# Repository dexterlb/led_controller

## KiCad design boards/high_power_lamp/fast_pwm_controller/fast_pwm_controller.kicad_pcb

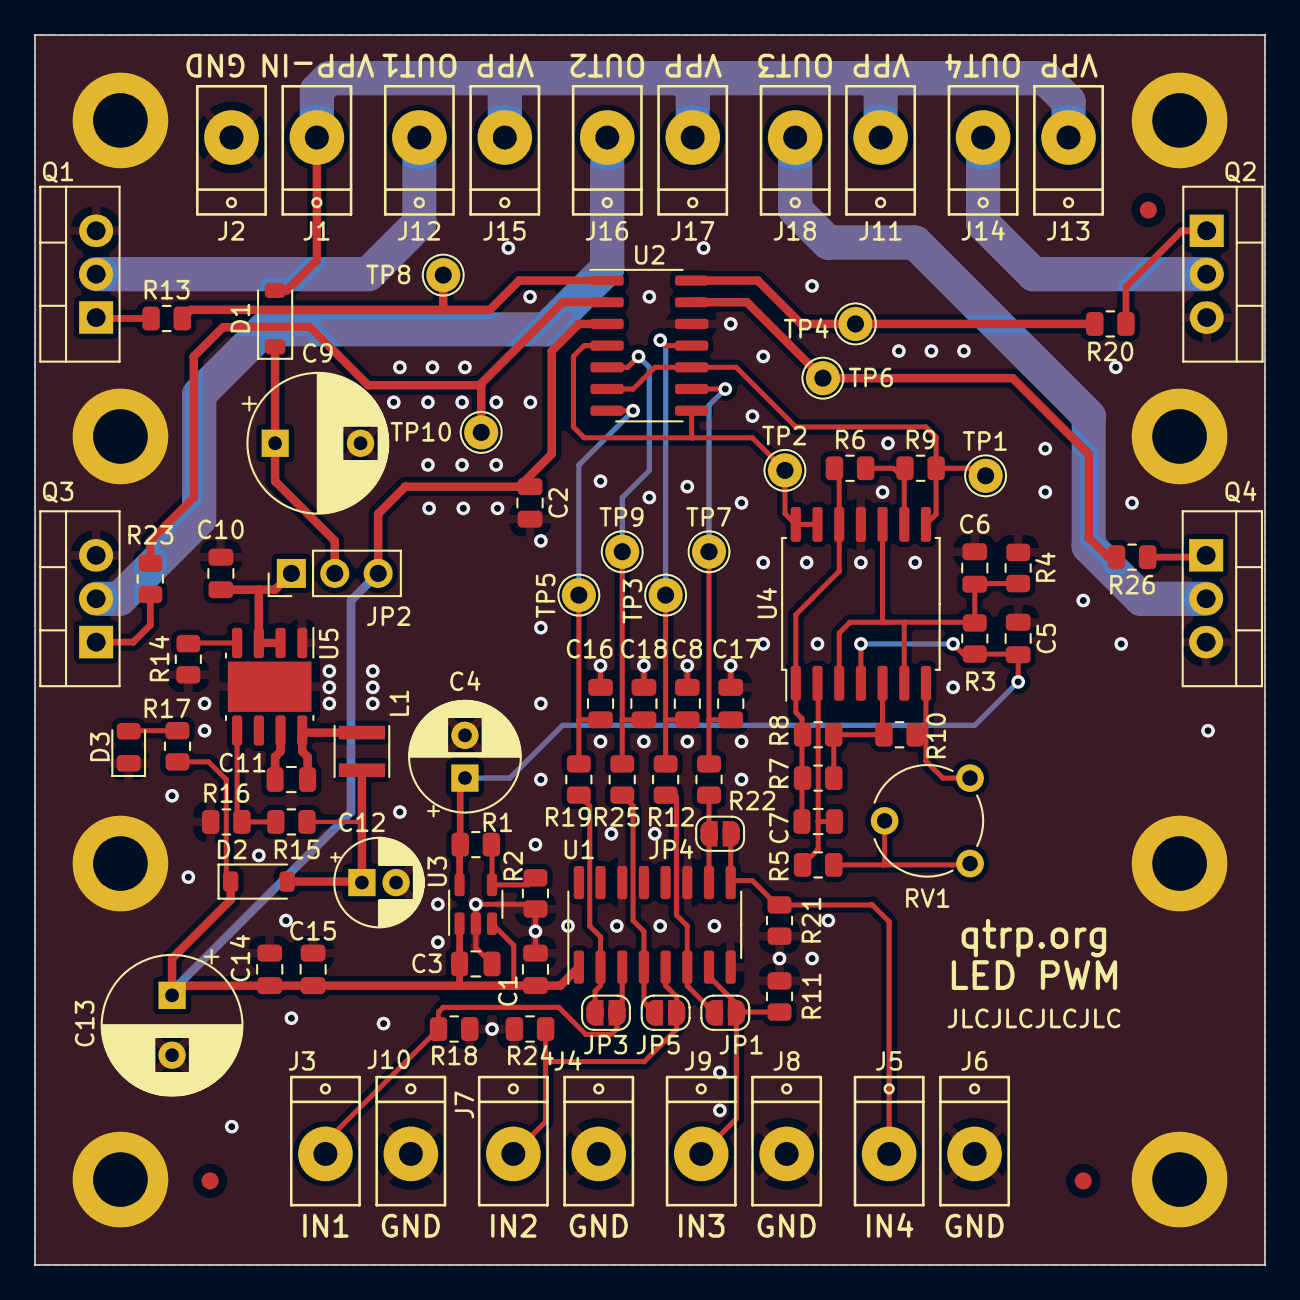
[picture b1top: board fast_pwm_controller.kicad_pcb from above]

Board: 2 copper layers, 72.0 x 72.0 mm, 102 parts (0 on the bottom side), 46 nets.

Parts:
C1, C2, C10, C11, C15: 100n; C_0805_2012Metric
C3, C5, C6: 100nF; C_0805_2012Metric
C4: 100μF; CP_Radial_D6.3mm_P2.50mm
C7: 1nF; C_0805_2012Metric
C8, C16, C17, C18: 500nF; C_0805_2012Metric
C9: 100μ; CP_Radial_D8.0mm_P5.00mm
C12: 22μ; CP_Radial_D5.0mm_P2.00mm
C13: 220μ; CP_Radial_D8.0mm_P3.50mm
C14: 1μ; C_0805_2012Metric
D1, D2: 1N4148; D_SOD-123
D3: GREEN LED; LED_0805_2012Metric
FID1, FID2, FID3: Fiducial; Fiducial_1mm_Mask2mm
H1, H2, H3, H4, H5, H6, H7, H8: MountingHole; MountingHole_3.2mm_M3_DIN965_Pad
J1, J2, J3, J4, J5, J6, J7, J8, J9, J10, J11, J12, J13, J14, J15, J16, J17, J18: Screw_Terminal_01x01; 1PIN_DG306
JP1, JP3, JP4, JP5: SolderJumper_2_Open; SolderJumper-2_P1.3mm_Open_RoundedPad1.0x1.5mm
JP2: Jumper_3; PinHeader_1x03_P2.54mm_Vertical
L1: 15μH; L_Taiyo-Yuden_MD-3030
Q1, Q2, Q3, Q4: BUK7516-55A,127; TO-220-3_Vertical
R1: 165k; R_0805_2012Metric
R2: 23.2k; R_0805_2012Metric
R3, R4: 10k; R_0805_2012Metric
R5, R17: 4.7k; R_0805_2012Metric
R6, R7, R9, R10: 22k; R_0805_2012Metric
R8: 1M; R_0805_2012Metric
R11, R18, R21, R24: 10M; R_0805_2012Metric
R12, R14, R19, R22, R25: 47k; R_0805_2012Metric
R13, R20, R23, R26: 2.2Ω; R_0805_2012Metric
R15: 120k; R_0805_2012Metric
R16: 10.2k; R_0805_2012Metric
RV1: 500k; Potentiometer_Piher_PT-6-V_Vertical
TP1, TP2, TP3, TP4, TP5, TP6, TP7, TP8, TP9, TP10: TestPoint; TestPoint_THTPad_D2.0mm_Drill1.0mm
U1: 4050; SOIC-16_3.9x9.9mm_P1.27mm
U2: TLC3704; SOIC-14_3.9x8.7mm_P1.27mm
U3: SPX5205-adjustable; SOT-23-5
U4: ADA4851-4; SOIC-14W_7.5x9mm_P1.27mm
U5: LMR380(10/20); Texas_R-PDSO-G8_EP2.95x4.9mm_Mask2.4x3.1mm

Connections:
+12V: C1.1, C2.1, C3.2, C13.1, C14.1, C15.1, D2.1 (K), JP2.3 (B), R17.2, U1.1 (VCC), U2.3 (V+), U3.1 (IN), U3.3 (EN)
/PWM stage 1/IN: J3.1, JP3.1 (A), R18.1, U1.3
/PWM stage 1/OUT: J12.1, Q1.2 (D)
/PWM stage 1/TRIANGLE: R9.2, TP1.1, U2.6 (-), U2.10 (-), U4.8
/PWM stage 2/IN: J7.1, JP5.1 (A), R24.1, U1.5
/PWM stage 2/OUT: J16.1, Q3.2 (D)
/PWM stage 2/TRIANGLE: TP2.1, U2.4 (-), U2.8 (-), U4.13 (-), U4.14
/PWM stage 3/IN: J9.1, JP1.1 (A), R11.1, U1.7
/PWM stage 3/OUT: J18.1, Q4.2 (D)
/PWM stage 4/IN: J5.1, JP4.1 (A), R21.1, U1.9
/PWM stage 4/OUT: J14.1, Q2.2 (D)
/Power supply/FB: R15.1, R16.2, U5.5 (FB)
/Power supply/PWR: C11.2, L1.1, U5.8 (SW)
/Triangle generator/SQUARE: R10.2, RV1.1, U4.7
/Triangle generator/TGEN_VCC: C4.1, C5.2, R1.2, R3.2, U3.5 (OUT), U4.4 (V+)
/Triangle generator/VMID: C6.2, R3.1, R4.2, U4.3 (+), U4.6 (-), U4.10 (+)
GND: C1.2, C2.2, C3.1, C4.2, C5.1, C6.1, C8.1, C9.2, C10.2, C12.2, C13.2, C14.2, C15.2, C16.1, C17.1, C18.1, D3.1 (K), H1.1, H2.1, H3.1, H4.1, H5.1, H6.1, H7.1, H8.1, J2.1, J4.1, J6.1, J8.1, J10.1, Q1.3 (S), Q2.3 (S), Q3.3 (S), Q4.3 (S), R2.1, R4.1, R11.2, R14.1, R16.1, R18.2, R21.2, R24.2, U1.8 (VSS), U1.11, U1.14, U2.12 (V-), U3.2 (GND), U4.11 (V-), U5.1 (PGND), U5.9 (PAD)
unnamed: C9.1, D1.1 (K), JP2.2 (C)
unnamed: C12.1, D2.2 (A), L1.2, R15.2
unnamed: D3.2 (A), R17.1
unnamed: JP1.2 (B), R12.2, U1.6
unnamed: C10.1, JP2.1 (A), U5.2 (EN), U5.3 (VIN)
unnamed: JP3.2 (B), R19.2, U1.2
unnamed: JP4.2 (B), R22.2, U1.10
unnamed: JP5.2 (B), R25.2, U1.4
unnamed: Q1.1 (G), R13.1
unnamed: Q2.1 (G), R20.1
unnamed: Q3.1 (G), R23.1
unnamed: Q4.1 (G), R26.1
unnamed: R5.1, RV1.2, RV1.3
unnamed: R13.2, TP8.1, U2.1
unnamed: R20.2, TP4.1, U2.14
unnamed: R23.2, TP10.1, U2.2
unnamed: R26.2, TP6.1, U2.13
unnamed: C18.2, R25.1, TP9.1, U2.5 (+)
unnamed: C16.2, R19.1, TP5.1, U2.7 (+)
unnamed: C8.2, R12.1, TP3.1, U2.11 (+)
unnamed: C17.2, R22.1, TP7.1, U2.9 (+)
unnamed: R1.1, R2.2, U3.4 (ADJ)
unnamed: C7.1, R5.2, U4.2 (-)
unnamed: R7.2, R8.2, R10.1, U4.5 (+)
unnamed: R6.2, R9.1, U4.9 (-)
unnamed: C7.2, R6.1, R7.1, R8.1, U4.1, U4.12 (+)
unnamed: C11.1, U5.7 (BOOT)
unnamed: R14.2, U5.4 (RT/SYNC)
VPP: D1.2 (A), J1.1, J11.1, J13.1, J15.1, J17.1

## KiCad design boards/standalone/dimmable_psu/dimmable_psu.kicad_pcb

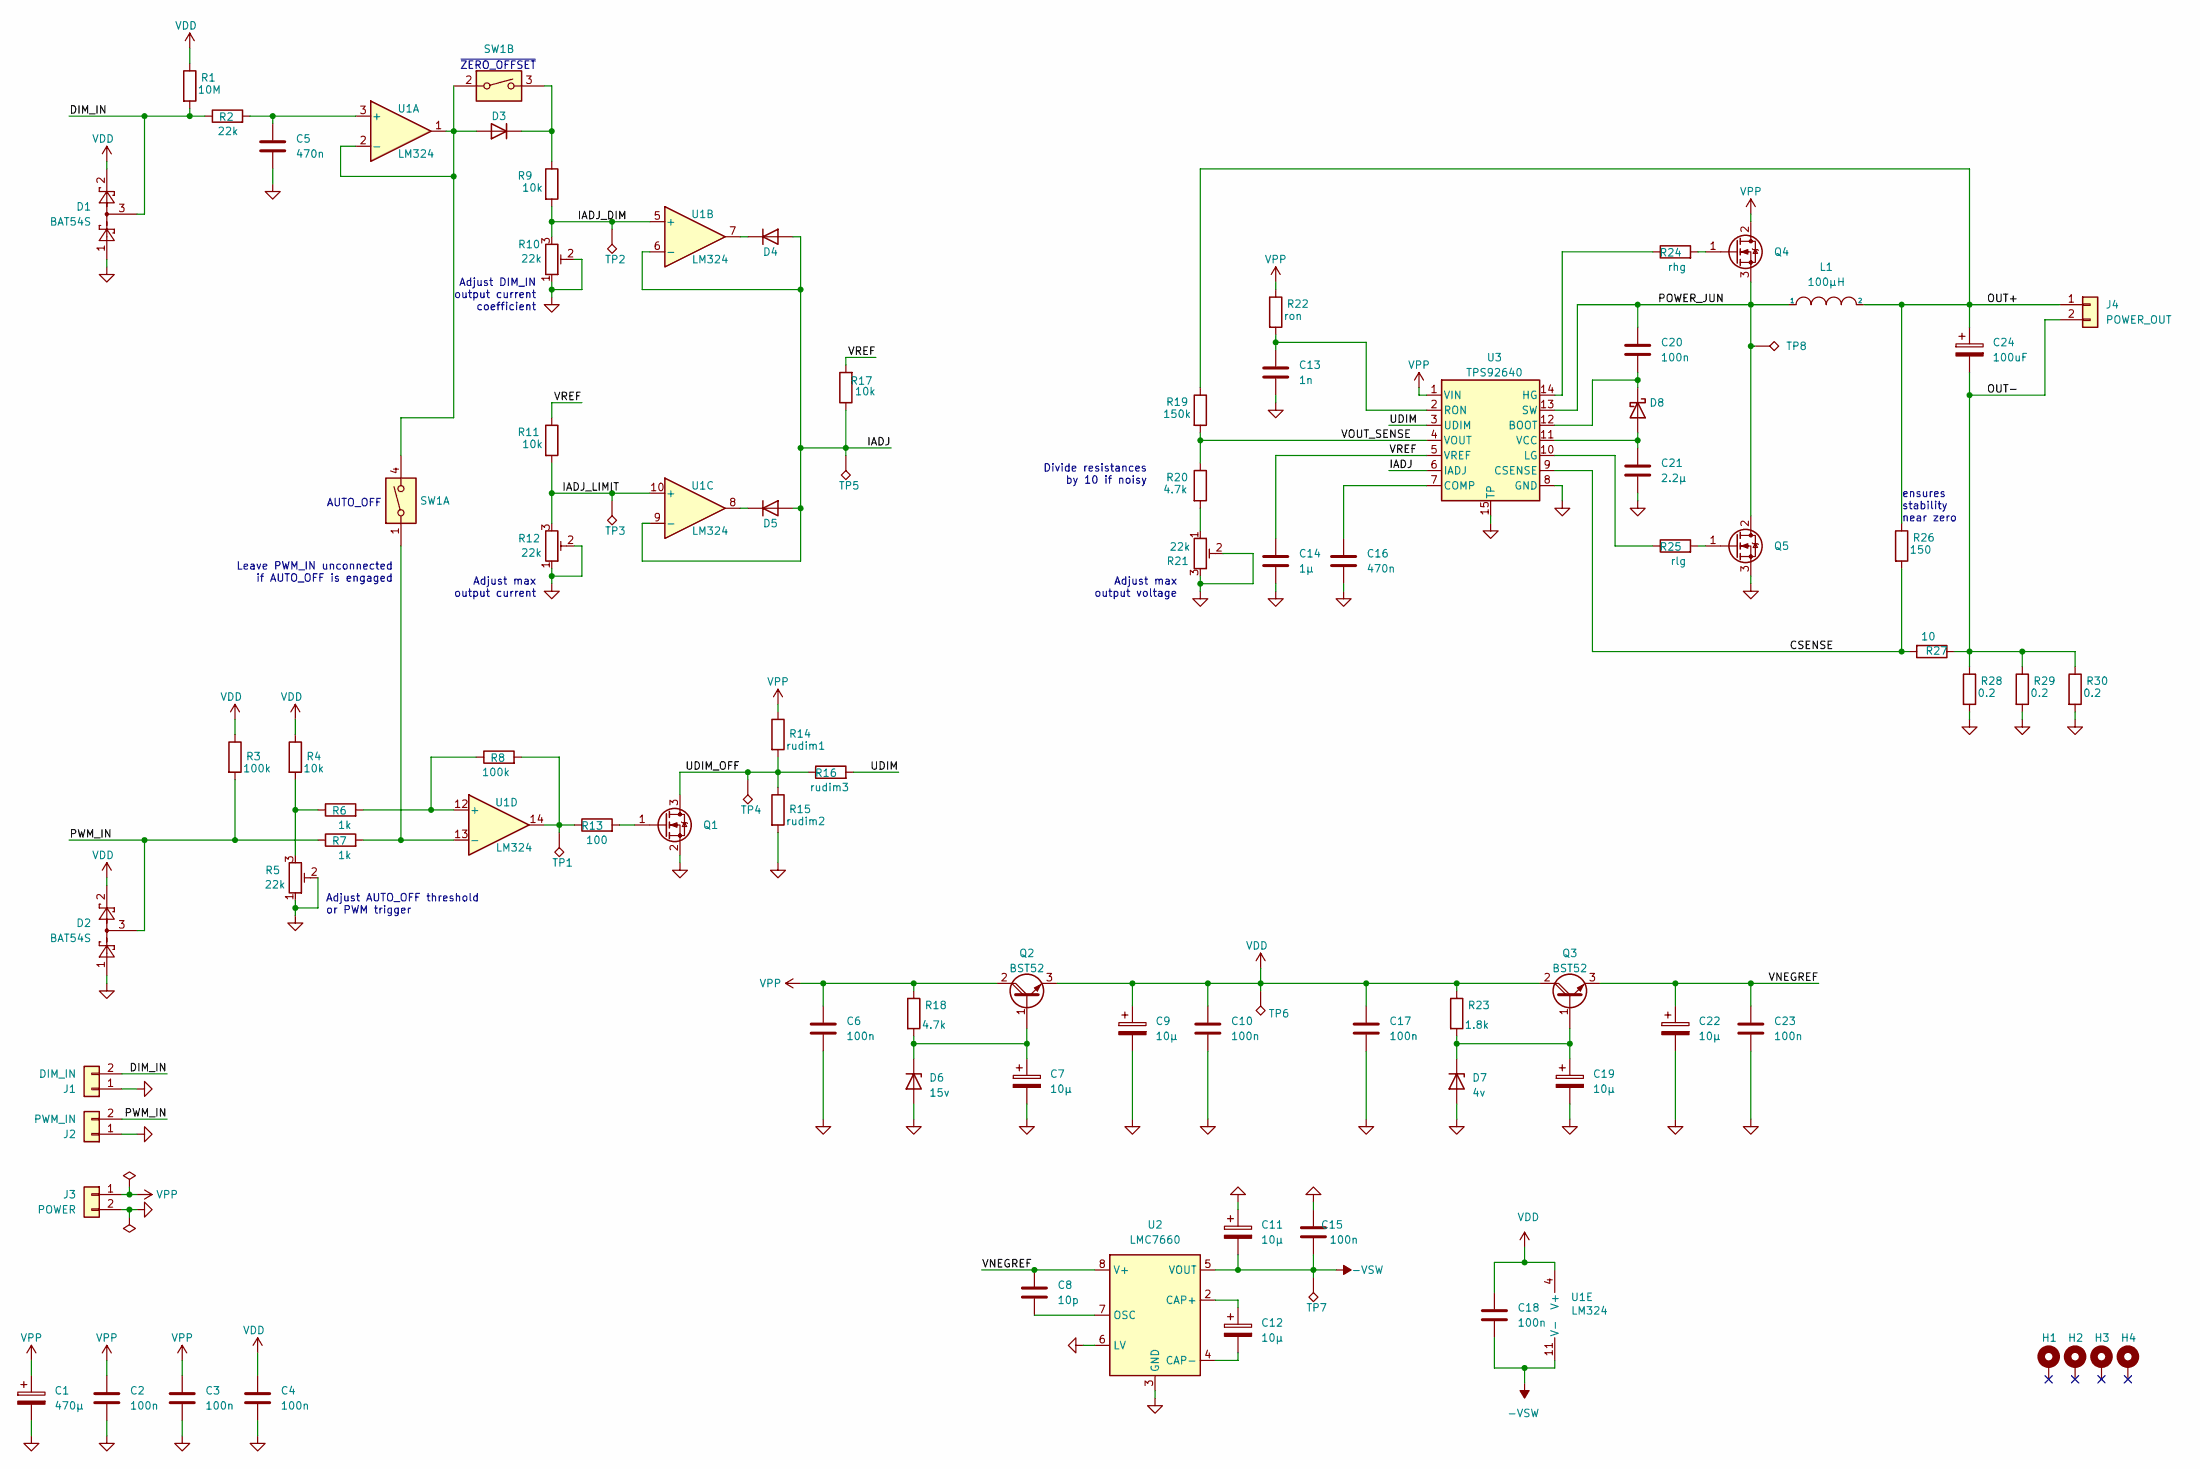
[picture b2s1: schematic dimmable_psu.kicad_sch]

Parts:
C1: 470µ; CP_Radial_D16.0mm_P7.50mm
C2, C3, C4, C6, C10, C15, C17, C18, C20, C23: 100n; C_0805_2012Metric_Pad1.18x1.45mm_HandSolder
C5, C16: 470n; C_0805_2012Metric_Pad1.18x1.45mm_HandSolder
C7, C9, C11, C12, C19, C22: 10µ; C_1206_3216Metric_Pad1.33x1.80mm_HandSolder
C8: 10p; C_0805_2012Metric_Pad1.18x1.45mm_HandSolder
C13: 1n; C_0805_2012Metric_Pad1.18x1.45mm_HandSolder
C14: 1µ; C_0805_2012Metric_Pad1.18x1.45mm_HandSolder
C21: 2.2µ; C_0805_2012Metric_Pad1.18x1.45mm_HandSolder
C24: 100uF; CP_Radial_D12.5mm_P5.00mm
D1, D2: BAT54S; SOT-23
D3, D4, D5: D; D_SOD-123
D6: 15v; D_SOD-323_HandSoldering
D7: 4v; D_SOD-323_HandSoldering
D8: D_Schottky; D_SOD-123
H1, H2, H3, H4: MountingHole_Pad; MountingHole_3.2mm_M3_Pad
J1: DIM_IN; 250-402
J2: PWM_IN; 250-402
J3: POWER; 2061-602
J4: POWER_OUT; 2061-602
L1: 100µH; L_Bourns_SRR1770
Q1: 2N7002; SOT-23
Q2, Q3: BST52; SOT-89-3
Q4, Q5: IRF540N; TO-220-3_Vertical
R1: 10M; R_0805_2012Metric_Pad1.20x1.40mm_HandSolder
R2: 22k; R_0805_2012Metric_Pad1.20x1.40mm_HandSolder
R3, R8: 100k; R_0805_2012Metric_Pad1.20x1.40mm_HandSolder
R4, R9, R11, R17: 10k; R_0805_2012Metric_Pad1.20x1.40mm_HandSolder
R5, R10, R12, R21: 22k; Potentiometer_Bourns_3296Y_Vertical
R6, R7: 1k; R_0805_2012Metric_Pad1.20x1.40mm_HandSolder
R13: 100; R_0805_2012Metric_Pad1.20x1.40mm_HandSolder
R14: rudim1; R_0805_2012Metric_Pad1.20x1.40mm_HandSolder
R15: rudim2; R_0805_2012Metric_Pad1.20x1.40mm_HandSolder
R16: rudim3; R_0805_2012Metric_Pad1.20x1.40mm_HandSolder
R18, R20: 4.7k; R_0805_2012Metric_Pad1.20x1.40mm_HandSolder
R19: 150k; R_0805_2012Metric_Pad1.20x1.40mm_HandSolder
R22: ron; R_0805_2012Metric_Pad1.20x1.40mm_HandSolder
R23: 1.8k; R_0805_2012Metric_Pad1.20x1.40mm_HandSolder
R24: rhg; R_0805_2012Metric_Pad1.20x1.40mm_HandSolder
R25: rlg; R_0805_2012Metric_Pad1.20x1.40mm_HandSolder
R26: 150; R_Axial_DIN0309_L9.0mm_D3.2mm_P12.70mm_Horizontal
R27: 10; R_Axial_DIN0309_L9.0mm_D3.2mm_P12.70mm_Horizontal
R28, R29, R30: 0.2; R_Axial_DIN0309_L9.0mm_D3.2mm_P12.70mm_Horizontal
SW1: SW_DIP_SPLIT_x02
TP1, TP2, TP3, TP4, TP5, TP6, TP7, TP8: TestPoint; TestPoint_THTPad_D2.0mm_Drill1.0mm
U1: LM324; SOIC-14_3.9x8.7mm_P1.27mm
U2: LMC7660; SOIC-8_3.9x4.9mm_P1.27mm
U3: TPS92640; HTSSOP-14-1EP_4.4x5mm_P0.65mm_EP3.4x5mm_Mask3x3.1mm

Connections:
-VSW: C11.2, C15.1, C18.2, TP7.1, U1.11 (V-), U2.5 (VOUT)
/CSENSE: R26.2, R27.2, U3.9 (CSENSE)
/DIM_IN: D1.3, J1.2, R1.2, R2.1
/IADJ: D4.2 (A), D5.2 (A), R17.1, TP5.1, U1.6 (-), U1.9 (-), U3.6 (IADJ)
/IADJ_DIM: R9.2, R10.3, TP2.1, U1.5 (+)
/IADJ_LIMIT: R11.2, R12.3, TP3.1, U1.10 (+)
/OUT+: C24.1, J4.1, L1.2, R19.1, R26.1
/OUT-: C24.2, J4.2, R27.1, R28.1, R29.1, R30.1
/POWER_JUN: C20.1, L1.1, Q4.3 (S), Q5.2 (D), TP8.1, U3.13 (SW)
/PWM_IN: D2.3, J2.2, R3.2, R7.1
/UDIM: R16.2, U3.3 (UDIM)
/UDIM_OFF: Q1.3 (D), R14.2, R15.1, R16.1, TP4.1
/VNEGREF: C8.1, C22.1, C23.1, Q3.3 (E), U2.8 (V+)
/VOUT_SENSE: R19.2, R20.1, U3.4 (VOUT)
/VREF: C14.1, R11.1, R17.2, U3.5 (VREF)
GND: C1.2, C2.2, C3.2, C4.2, C5.2, C6.2, C7.2, C9.2, C10.2, C11.1, C13.2, C14.2, C15.2, C16.2, C17.2, C19.2, C21.2, C22.2, C23.2, D1.1, D2.1, D6.2 (A), D7.2 (A), J1.1, J2.1, J3.2, Q1.2 (S), Q5.3 (S), R5.1, R5.2, R10.1, R10.2, R12.1, R12.2, R15.2, R21.2, R21.3, R28.2, R29.2, R30.2, U2.3 (GND), U2.6 (LV), U3.8 (GND), U3.15 (TP)
unnamed: C5.1, R2.2, U1.3 (+)
unnamed: C7.1, D6.1 (K), Q2.1 (B), R18.2
unnamed: C8.2, U2.7 (OSC)
unnamed: C12.1, U2.2 (CAP+)
unnamed: C12.2, U2.4 (CAP-)
unnamed: C13.1, R22.2, U3.2 (RON)
unnamed: C16.1, U3.7 (COMP)
unnamed: C19.1, D7.1 (K), Q3.1 (B), R23.2
unnamed: C20.2, D8.1 (K), U3.12 (BOOT)
unnamed: C21.1, D8.2 (A), U3.11 (VCC)
unnamed: D3.1 (K), R9.1, SW1.3
unnamed: D3.2 (A), SW1.2, SW1.4, U1.1, U1.2 (-)
unnamed: D4.1 (K), U1.7
unnamed: D5.1 (K), U1.8
unnamed: Q1.1 (G), R13.2
unnamed: Q4.1 (G), R24.2
unnamed: Q5.1 (G), R25.2
unnamed: R4.2, R5.3, R6.1
unnamed: R6.2, R8.1, U1.12 (+)
unnamed: R7.2, SW1.1, U1.13 (-)
unnamed: R8.2, R13.1, TP1.1, U1.14
unnamed: R20.2, R21.1
unnamed: R24.1, U3.14 (HG)
unnamed: R25.1, U3.10 (LG)
VDD: C4.1, C9.1, C10.1, C17.1, C18.1, D1.2, D2.2, Q2.3 (E), Q3.2 (C), R1.1, R3.1, R4.1, R23.1, TP6.1, U1.4 (V+)
VPP: C1.1, C2.1, C3.1, C6.1, J3.1, Q2.2 (C), Q4.2 (D), R14.1, R18.1, R22.1, U3.1 (VIN)

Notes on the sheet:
Adjust AUTO_OFF threshold or PWM trigger
AUTO_OFF
Leave PWM_IN unconnected if AUTO_OFF is engaged
~{ZERO_OFFSET}
Adjust DIM_IN output current coefficient
Adjust max output current
Divide resistances by 10 if noisy
Adjust max output voltage
ensures stability near zero

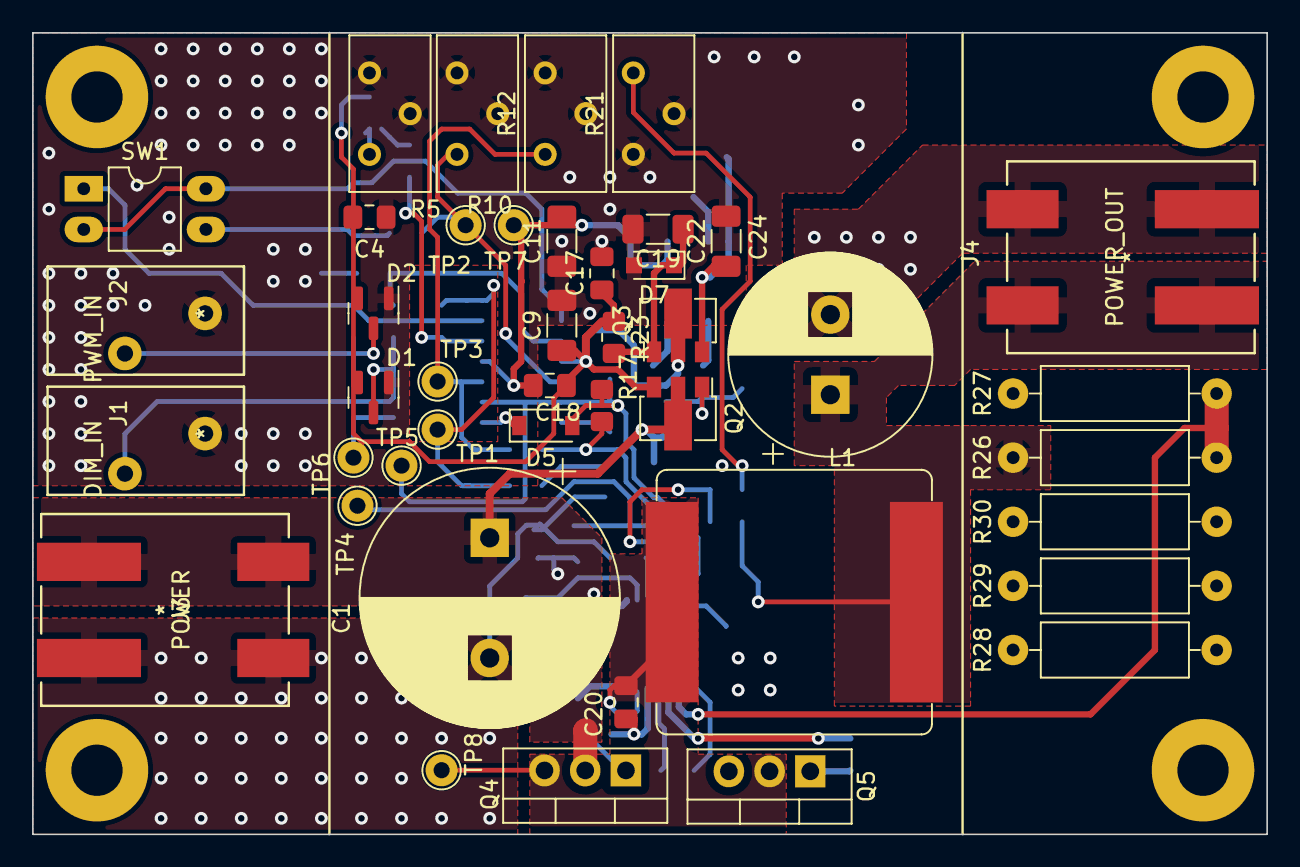
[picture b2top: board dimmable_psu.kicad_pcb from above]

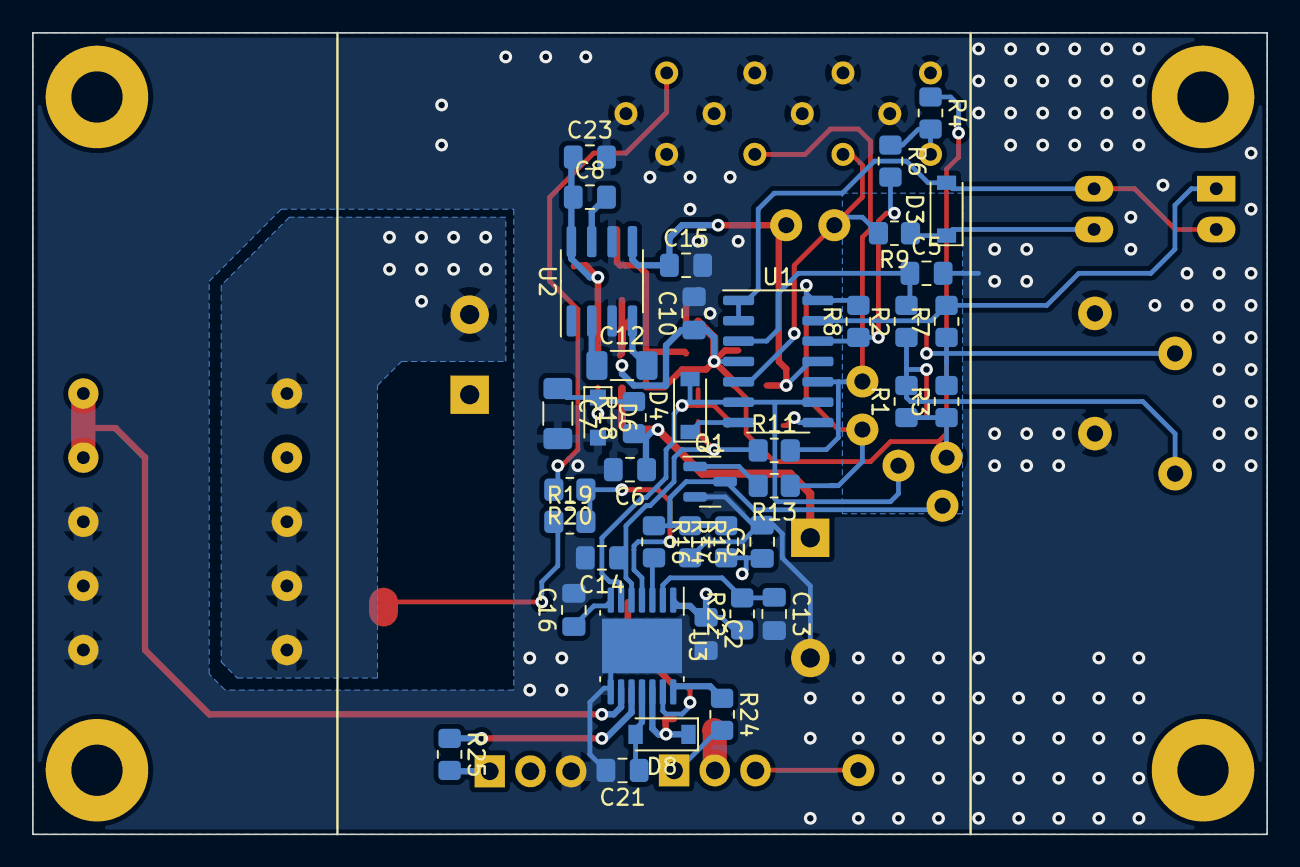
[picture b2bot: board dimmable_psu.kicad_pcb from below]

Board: 2 copper layers, 77.0 x 50.0 mm, 88 parts (41 on the bottom side), 42 nets.

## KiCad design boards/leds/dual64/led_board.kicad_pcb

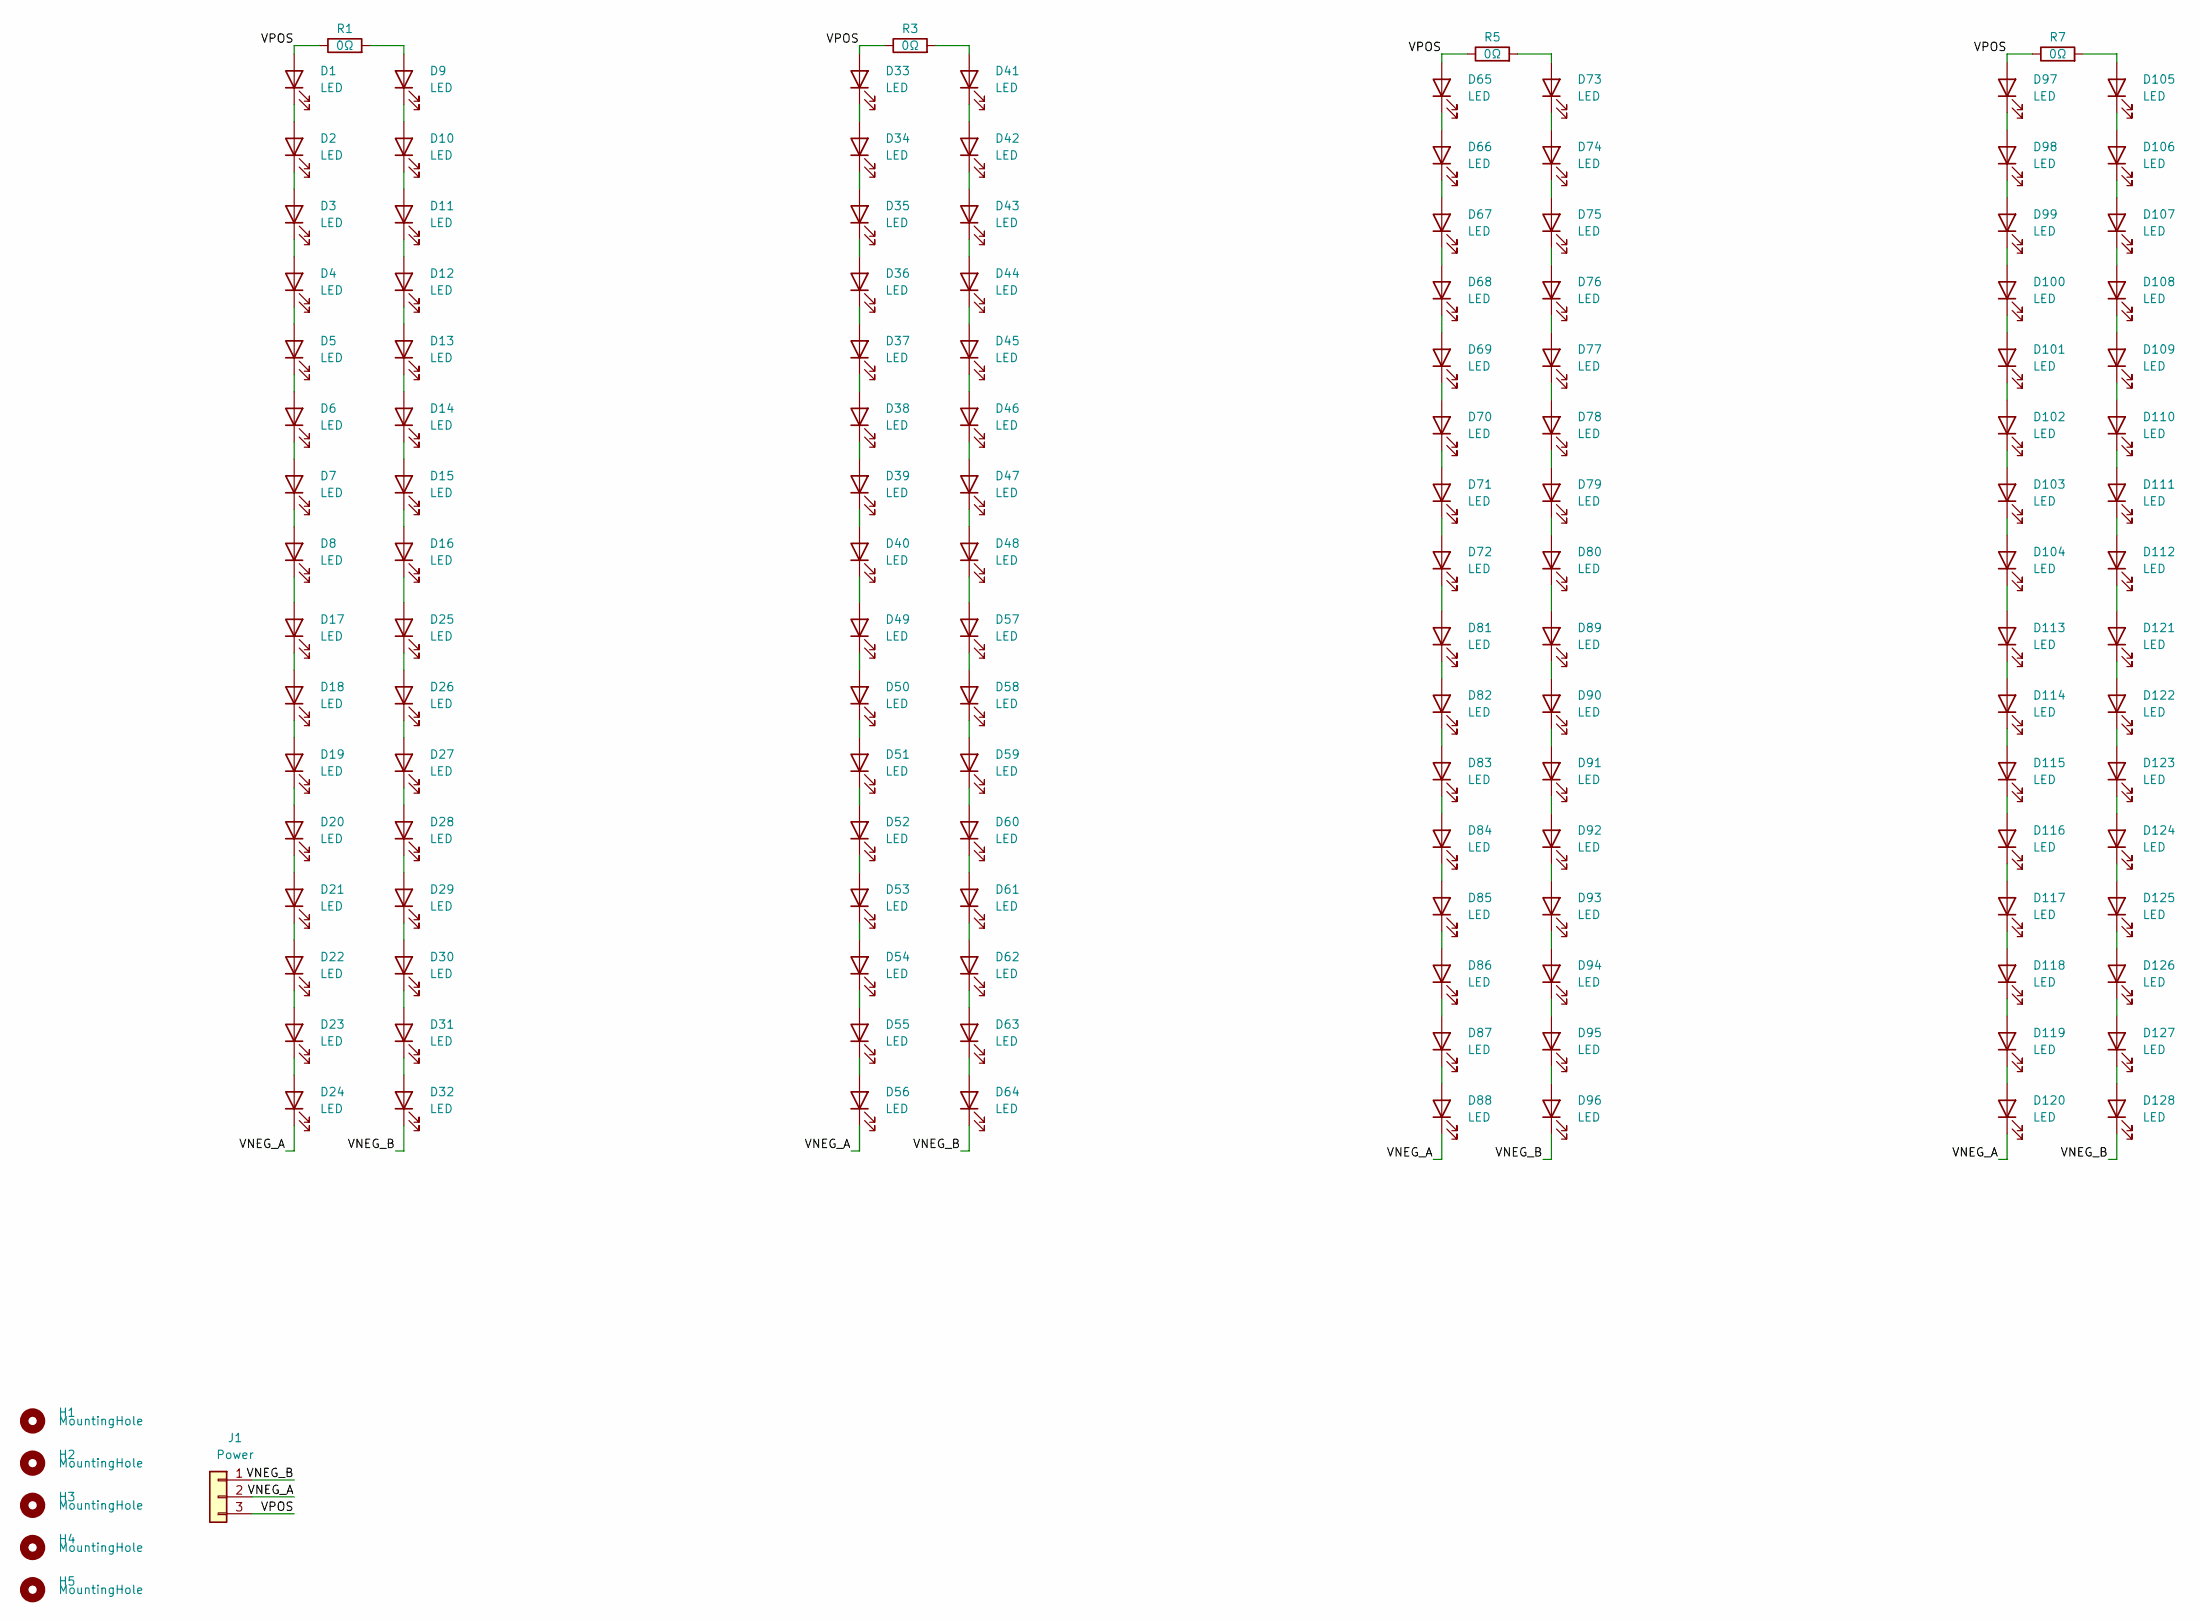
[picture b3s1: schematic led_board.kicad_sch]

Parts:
D1, D2, D3, D4, D5, D6, D7, D8, D9, D10, D11, D12, D13, D14, D15, D16, D17, D18, D19, D20, D21, D22, D23, D24, D25, D26, D27, D28, D29, D30, D31, D32, D33, D34, D35, D36, D37, D38, D39, D40, D41, D42, D43, D44, D45, D46, D47, D48, D49, D50, D51, D52, D53, D54, D55, D56, D57, D58, D59, D60, D61, D62, D63, D64, D65, D66, D67, D68, D69, D70, D71, D72, D73, D74, D75, D76, D77, D78, D79, D80, D81, D82, D83, D84, D85, D86, D87, D88, D89, D90, D91, D92, D93, D94, D95, D96, D97, D98, D99, D100, D101, D102, D103, D104, D105, D106, D107, D108, D109, D110, D111, D112, D113, D114, D115, D116, D117, D118, D119, D120, D121, D122, D123, D124, D125, D126, D127, D128: LED; LED_PLCC_2835_Handsoldering
H1, H2, H3, H4, H5: MountingHole; MountingHole_3.2mm_M3
J1: Power; wago-2060-453
R1, R3, R5, R7: 0Ω; R_2010_5025Metric_Pad1.40x2.65mm_HandSolder

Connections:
/VNEG_A: D24.1 (K), D56.1 (K), D88.1 (K), D120.1 (K), J1.2
/VNEG_B: D32.1 (K), D64.1 (K), D96.1 (K), D128.1 (K), J1.1
unnamed: D1.1 (K), D2.2 (A)
unnamed: D2.1 (K), D3.2 (A)
unnamed: D3.1 (K), D4.2 (A)
unnamed: D4.1 (K), D5.2 (A)
unnamed: D5.1 (K), D6.2 (A)
unnamed: D6.1 (K), D7.2 (A)
unnamed: D7.1 (K), D8.2 (A)
unnamed: D10.1 (K), D11.2 (A)
unnamed: D9.1 (K), D10.2 (A)
unnamed: D11.1 (K), D12.2 (A)
unnamed: D12.1 (K), D13.2 (A)
unnamed: D13.1 (K), D14.2 (A)
unnamed: D14.1 (K), D15.2 (A)
unnamed: D15.1 (K), D16.2 (A)
unnamed: D16.1 (K), D25.2 (A)
unnamed: D17.1 (K), D18.2 (A)
unnamed: D8.1 (K), D17.2 (A)
unnamed: D18.1 (K), D19.2 (A)
unnamed: D19.1 (K), D20.2 (A)
unnamed: D20.1 (K), D21.2 (A)
unnamed: D21.1 (K), D22.2 (A)
unnamed: D22.1 (K), D23.2 (A)
unnamed: D23.1 (K), D24.2 (A)
unnamed: D25.1 (K), D26.2 (A)
unnamed: D26.1 (K), D27.2 (A)
unnamed: D27.1 (K), D28.2 (A)
unnamed: D28.1 (K), D29.2 (A)
unnamed: D29.1 (K), D30.2 (A)
unnamed: D30.1 (K), D31.2 (A)
unnamed: D31.1 (K), D32.2 (A)
unnamed: D33.1 (K), D34.2 (A)
unnamed: D34.1 (K), D35.2 (A)
unnamed: D35.1 (K), D36.2 (A)
unnamed: D36.1 (K), D37.2 (A)
unnamed: D37.1 (K), D38.2 (A)
unnamed: D38.1 (K), D39.2 (A)
unnamed: D39.1 (K), D40.2 (A)
unnamed: D40.1 (K), D49.2 (A)
unnamed: D41.1 (K), D42.2 (A)
unnamed: D41.2 (A), R3.2
unnamed: D42.1 (K), D43.2 (A)
unnamed: D43.1 (K), D44.2 (A)
unnamed: D44.1 (K), D45.2 (A)
unnamed: D45.1 (K), D46.2 (A)
unnamed: D46.1 (K), D47.2 (A)
unnamed: D47.1 (K), D48.2 (A)
unnamed: D48.1 (K), D57.2 (A)
unnamed: D49.1 (K), D50.2 (A)
unnamed: D50.1 (K), D51.2 (A)
unnamed: D51.1 (K), D52.2 (A)
unnamed: D52.1 (K), D53.2 (A)
unnamed: D53.1 (K), D54.2 (A)
unnamed: D54.1 (K), D55.2 (A)
unnamed: D55.1 (K), D56.2 (A)
unnamed: D57.1 (K), D58.2 (A)
unnamed: D58.1 (K), D59.2 (A)
unnamed: D59.1 (K), D60.2 (A)
unnamed: D60.1 (K), D61.2 (A)
unnamed: D61.1 (K), D62.2 (A)
unnamed: D62.1 (K), D63.2 (A)
unnamed: D63.1 (K), D64.2 (A)
unnamed: D65.1 (K), D66.2 (A)
unnamed: D66.1 (K), D67.2 (A)
unnamed: D67.1 (K), D68.2 (A)
unnamed: D68.1 (K), D69.2 (A)
unnamed: D69.1 (K), D70.2 (A)
unnamed: D70.1 (K), D71.2 (A)
unnamed: D71.1 (K), D72.2 (A)
unnamed: D72.1 (K), D81.2 (A)
unnamed: D73.1 (K), D74.2 (A)
unnamed: D73.2 (A), R5.2
unnamed: D74.1 (K), D75.2 (A)
unnamed: D75.1 (K), D76.2 (A)
unnamed: D76.1 (K), D77.2 (A)
unnamed: D77.1 (K), D78.2 (A)
unnamed: D78.1 (K), D79.2 (A)
unnamed: D79.1 (K), D80.2 (A)
unnamed: D80.1 (K), D89.2 (A)
unnamed: D81.1 (K), D82.2 (A)
unnamed: D82.1 (K), D83.2 (A)
unnamed: D83.1 (K), D84.2 (A)
unnamed: D84.1 (K), D85.2 (A)
unnamed: D85.1 (K), D86.2 (A)
unnamed: D86.1 (K), D87.2 (A)
unnamed: D87.1 (K), D88.2 (A)
unnamed: D89.1 (K), D90.2 (A)
unnamed: D90.1 (K), D91.2 (A)
unnamed: D91.1 (K), D92.2 (A)
unnamed: D92.1 (K), D93.2 (A)
unnamed: D93.1 (K), D94.2 (A)
unnamed: D94.1 (K), D95.2 (A)
unnamed: D95.1 (K), D96.2 (A)
unnamed: D97.1 (K), D98.2 (A)
unnamed: D98.1 (K), D99.2 (A)
unnamed: D100.1 (K), D101.2 (A)
unnamed: D99.1 (K), D100.2 (A)
unnamed: D101.1 (K), D102.2 (A)
unnamed: D102.1 (K), D103.2 (A)
unnamed: D103.1 (K), D104.2 (A)
unnamed: D104.1 (K), D113.2 (A)
unnamed: D105.1 (K), D106.2 (A)
unnamed: D105.2 (A), R7.2
unnamed: D106.1 (K), D107.2 (A)
unnamed: D107.1 (K), D108.2 (A)
unnamed: D108.1 (K), D109.2 (A)
unnamed: D109.1 (K), D110.2 (A)
unnamed: D110.1 (K), D111.2 (A)
unnamed: D111.1 (K), D112.2 (A)
unnamed: D112.1 (K), D121.2 (A)
unnamed: D113.1 (K), D114.2 (A)
unnamed: D114.1 (K), D115.2 (A)
unnamed: D115.1 (K), D116.2 (A)
unnamed: D116.1 (K), D117.2 (A)
unnamed: D117.1 (K), D118.2 (A)
unnamed: D118.1 (K), D119.2 (A)
unnamed: D119.1 (K), D120.2 (A)
unnamed: D121.1 (K), D122.2 (A)
unnamed: D122.1 (K), D123.2 (A)
unnamed: D123.1 (K), D124.2 (A)
unnamed: D124.1 (K), D125.2 (A)
unnamed: D125.1 (K), D126.2 (A)
unnamed: D126.1 (K), D127.2 (A)
unnamed: D127.1 (K), D128.2 (A)

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
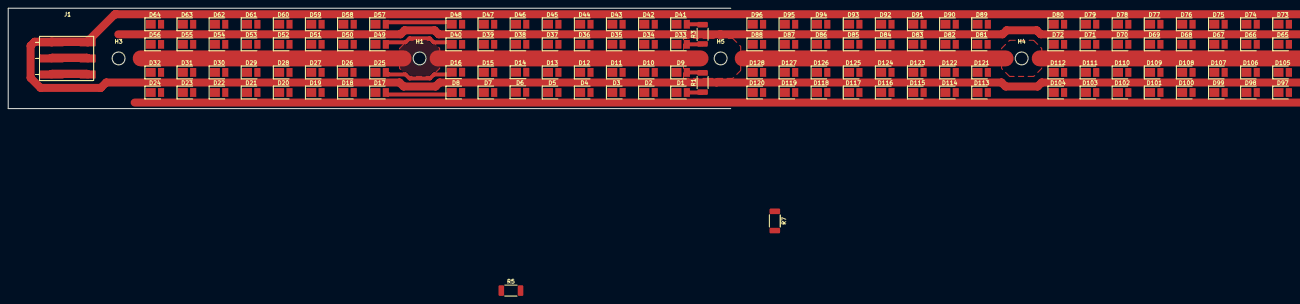
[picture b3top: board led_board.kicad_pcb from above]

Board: 2 copper layers, 138 parts (0 on the bottom side), 127 nets.

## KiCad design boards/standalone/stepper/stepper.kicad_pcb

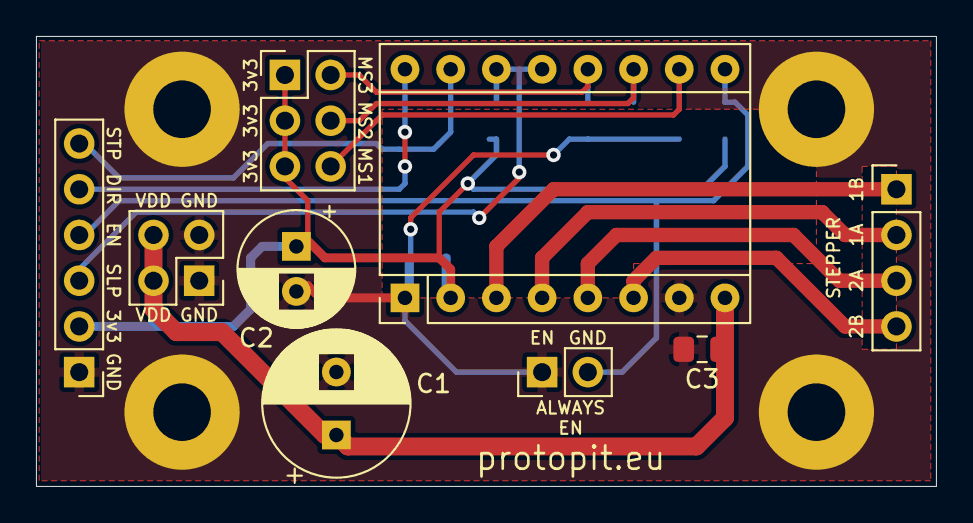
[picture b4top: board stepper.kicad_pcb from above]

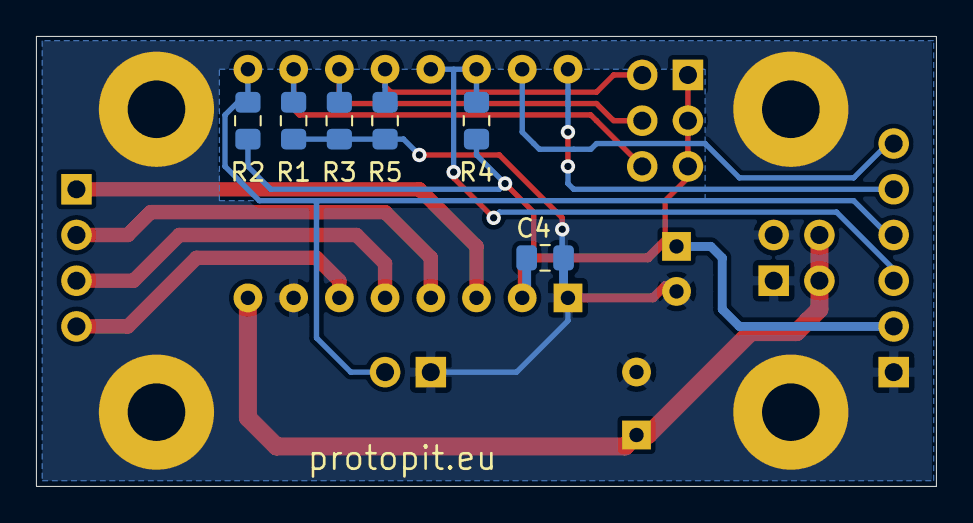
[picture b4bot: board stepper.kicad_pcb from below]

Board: 2 copper layers, 50.0 x 25.0 mm, 15 parts (6 on the bottom side), 14 nets.

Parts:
A1: Pololu_Breakout_A4988; Pololu_Breakout-16_15.2x20.3mm
C1: CP1; CP_Radial_D8.0mm_P3.50mm
C2: CP1; CP_Radial_D6.3mm_P2.50mm
C3, C4: C; C_0805_2012Metric_Pad1.15x1.40mm_HandSolder
J1: VDD_IN; PinHeader_2x02_P2.54mm_Vertical
J2: In; PinHeader_1x06_P2.54mm_Vertical
J3: Jumpers; PinHeader_2x03_P2.54mm_Vertical
J4: Stepper; PinHeader_1x04_P2.54mm_Vertical
JP1: EN_ALWAYS; PinHeader_1x02_P2.54mm_Vertical
R1, R2, R3, R4, R5: 10k; R_0805_2012Metric_Pad1.15x1.40mm_HandSolder

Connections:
+3V3: A1.2 (VDD), C2.1, C4.1, J2.2, J3.1, J3.3, J3.5, R2.1, R4.1
/DIR: A1.16 (DIR), J2.5
/ENABLE: A1.9 (~ENABLE), J2.4, JP1.2, R2.2
/SLEEP: A1.13 (~RESET), A1.14 (~SLEEP), J2.3, R4.2
/STEP: A1.15 (STEP), J2.6
GND: A1.1 (GND), A1.7 (GND), C1.2, C2.2, C3.2, C4.2, J1.1, J1.3, J2.1, JP1.1, R1.2, R3.2, R5.2
unnamed: A1.3 (1B), J4.1
unnamed: A1.4 (1A), J4.2
unnamed: A1.5 (2A), J4.3
unnamed: A1.6 (2B), J4.4
unnamed: A1.10 (MS1), J3.6, R1.1
unnamed: A1.11 (MS2), J3.4, R3.1
unnamed: A1.12 (MS3), J3.2, R5.1
VDD: A1.8 (VMOT), C1.1, C3.1, J1.2, J1.4

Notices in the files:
parts and their libraries:
Copyright 2016 Accelerated Designs. All rights reserved.
